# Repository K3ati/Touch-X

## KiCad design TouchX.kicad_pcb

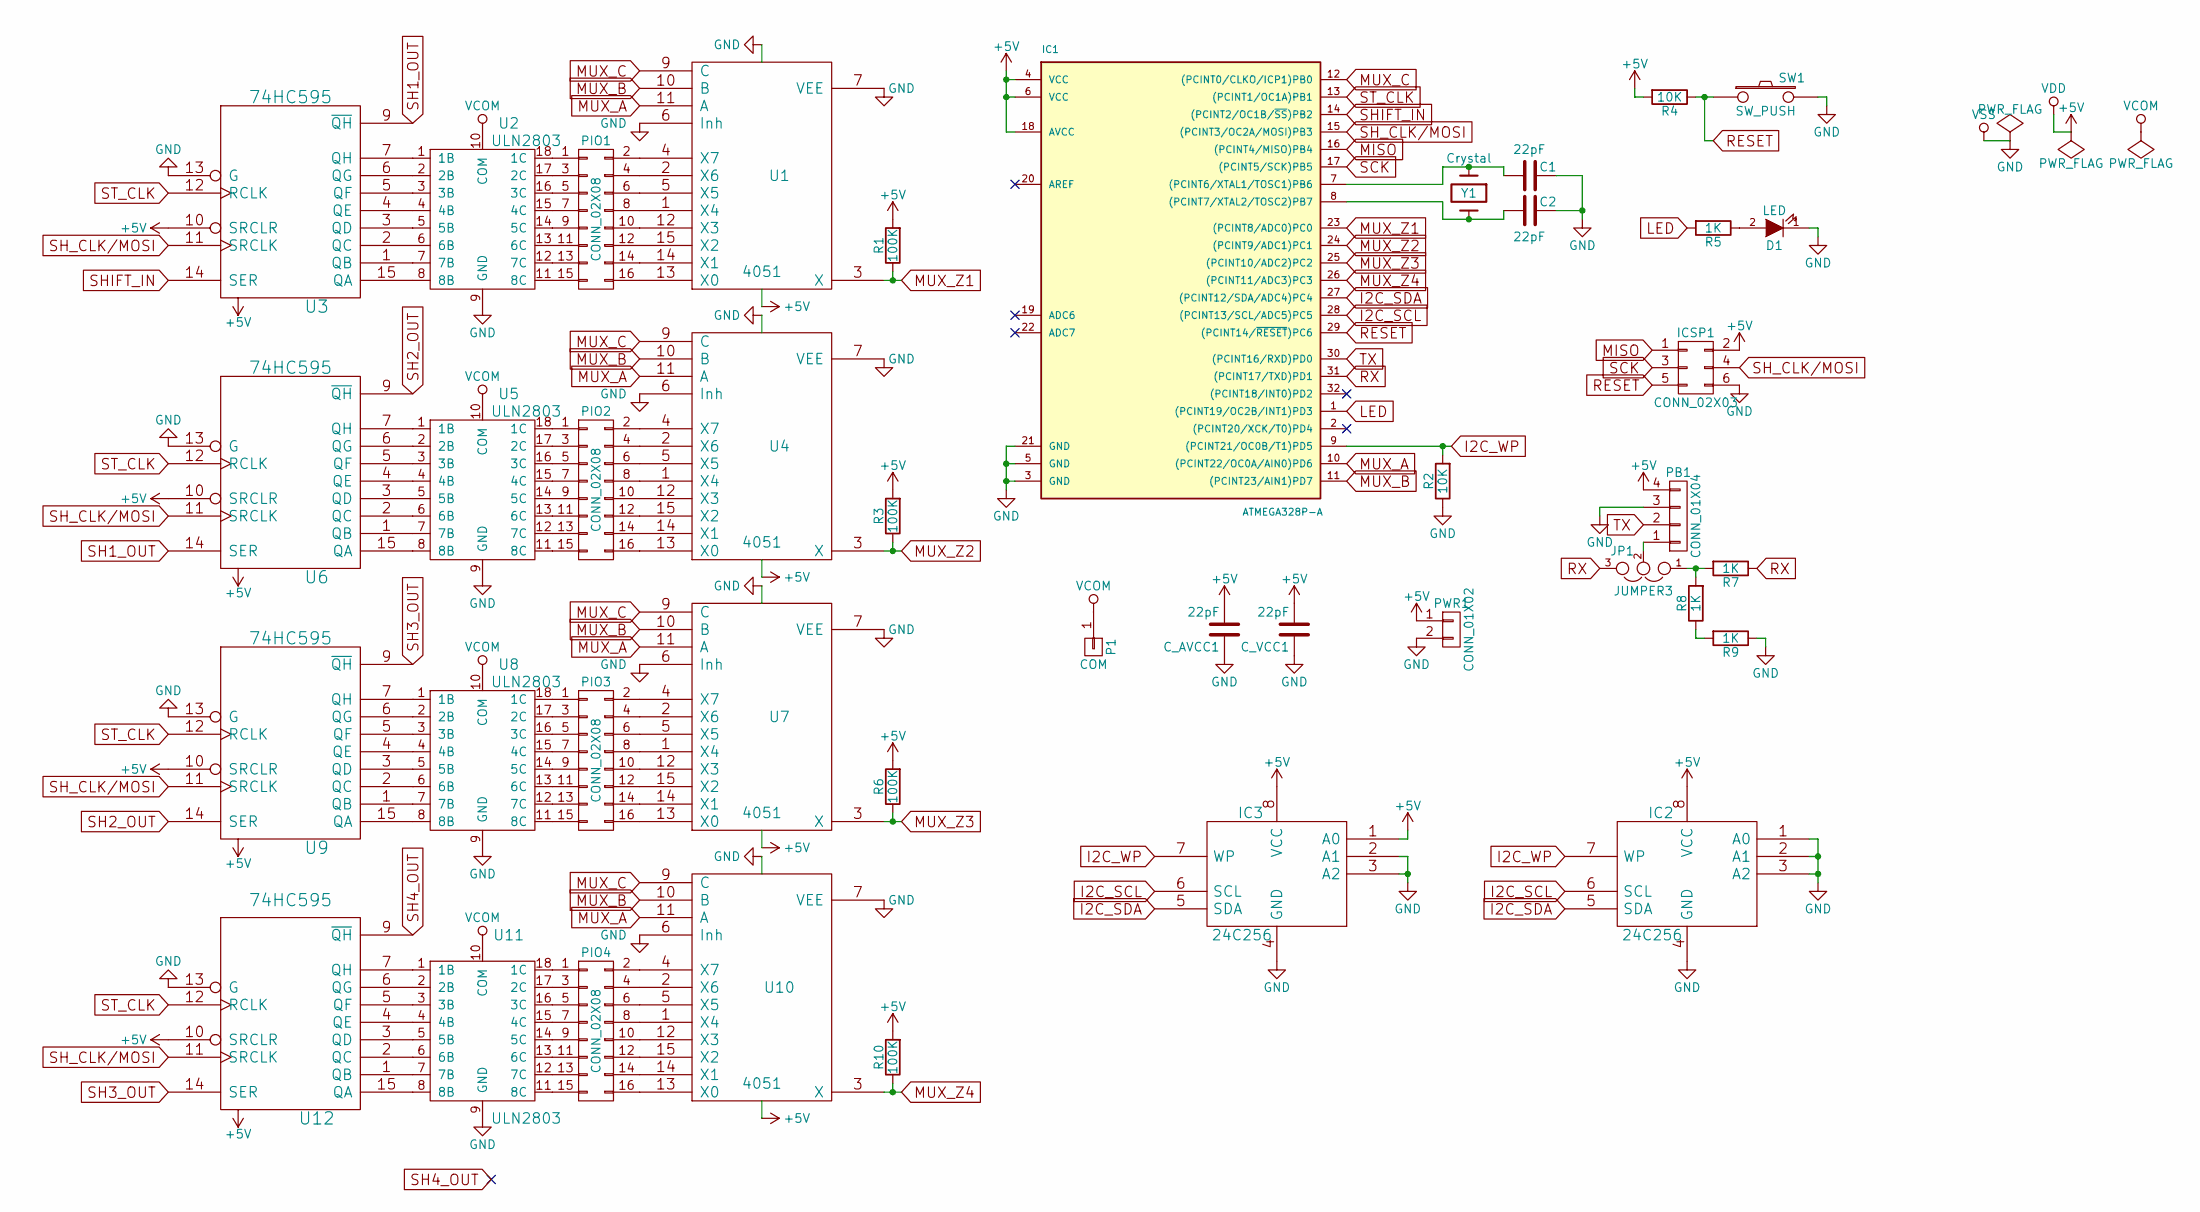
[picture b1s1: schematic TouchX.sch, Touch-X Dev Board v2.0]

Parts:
C1, C2: 22pF; c_1206
C_AVCC1: 22pF; c_1206
C_VCC1: 22pF; c_1206
D1: LED; Led_0805
IC1: ATMEGA328P-A; lqfp32
IC2, IC3: 24C256; so-8
ICSP1: CONN_02X03; pin_socket_3x2
JP1: JUMPER3; NetTie-II_SMD
P1: COM; Measurement_Point_Square-TH_Big
PB1: CONN_01X04; pin_socket_4
PIO1, PIO2, PIO3, PIO4: CONN_02X08; pin_socket_8x2
PWR1: CONN_01X02; pin_strip_2
R1, R3, R6, R10: 100K; r_1206
R2, R4: 10K; r_1206
R5, R7, R8, R9: 1K; r_1206
SW1: SW_PUSH; smd_push2
U1, U4, U7, U10: 4051; so-16
U2, U5, U8, U11: ULN2803; uln2803
U3, U6, U9, U12: 74HC595; so-16
Y1: Crystal; crystal_hc-49s

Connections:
+5V: C_AVCC1.2, C_VCC1.2, IC1.4 (VCC), IC1.6 (VCC), IC1.18 (AVCC), IC2.8 (VCC), IC3.1 (A0), IC3.8 (VCC), ICSP1.2, PB1.4, PWR1.1, R1.2, R3.2, R4.2, R6.2, R10.2, U1.16 (VDD), U3.10 (SRCLR), U3.16 (VCC), U4.16 (VDD), U6.10 (SRCLR), U6.16 (VCC), U7.16 (VDD), U9.10 (SRCLR), U9.16 (VCC), U10.16 (VDD), U12.10 (SRCLR), U12.16 (VCC)
GND: C1.1, C2.1, C_AVCC1.1, C_VCC1.1, D1.1 (K), IC1.3 (GND), IC1.5 (GND), IC1.21 (GND), IC2.1 (A0), IC2.2 (A1), IC2.3 (A2), IC2.4 (GND), IC3.2 (A1), IC3.3 (A2), IC3.4 (GND), ICSP1.6, PB1.3, PWR1.2, R2.1, R9.1, SW1.2, U1.6 (Inh), U1.7 (VEE), U1.8 (VSS), U2.9 (GND), U3.8 (GND), U3.13 (G), U4.6 (Inh), U4.7 (VEE), U4.8 (VSS), U5.9 (GND), U6.8 (GND), U6.13 (G), U7.6 (Inh), U7.7 (VEE), U7.8 (VSS), U8.9 (GND), U9.8 (GND), U9.13 (G), U10.6 (Inh), U10.7 (VEE), U10.8 (VSS), U11.9 (GND), U12.8 (GND), U12.13 (G)
I2C_SCL: IC1.28 ((PCINT13/SCL/ADC5)PC5), IC2.6 (SCL), IC3.6 (SCL)
I2C_SDA: IC1.27 ((PCINT12/SDA/ADC4)PC4), IC2.5 (SDA), IC3.5 (SDA)
I2C_WP: IC1.9 ((PCINT21/OC0B/T1)PD5), IC2.7 (WP), IC3.7 (WP), R2.2
LED: IC1.1 ((PCINT19/OC2B/INT1)PD3), R5.2
MISO: IC1.16 ((PCINT4/MISO)PB4), ICSP1.1
MUX_A: IC1.10 ((PCINT22/OC0A/AIN0)PD6), U1.11 (A), U4.11 (A), U7.11 (A), U10.11 (A)
MUX_B: IC1.11 ((PCINT23/AIN1)PD7), U1.10 (B), U4.10 (B), U7.10 (B), U10.10 (B)
MUX_C: IC1.12 ((PCINT0/CLKO/ICP1)PB0), U1.9 (C), U4.9 (C), U7.9 (C), U10.9 (C)
MUX_Z1: IC1.23 ((PCINT8/ADC0)PC0), R1.1, U1.3 (X)
MUX_Z2: IC1.24 ((PCINT9/ADC1)PC1), R3.1, U4.3 (X)
MUX_Z3: IC1.25 ((PCINT10/ADC2)PC2), R6.1, U7.3 (X)
MUX_Z4: IC1.26 ((PCINT11/ADC3)PC3), R10.1, U10.3 (X)
unnamed: C1.2, IC1.7 ((PCINT6/XTAL1/TOSC1)PB6), Y1.1
unnamed: C2.2, IC1.8 ((PCINT7/XTAL2/TOSC2)PB7), Y1.2
unnamed: D1.2 (A), R5.1
unnamed: JP1.1, R7.2, R8.2
unnamed: JP1.2, PB1.1
unnamed: PIO1.1, U2.18 (1C)
unnamed: PIO1.2, U1.4 (X7)
unnamed: PIO1.3, U2.17 (2C)
unnamed: PIO1.4, U1.2 (X6)
unnamed: PIO1.5, U2.16 (3C)
unnamed: PIO1.6, U1.5 (X5)
unnamed: PIO1.7, U2.15 (4C)
unnamed: PIO1.8, U1.1 (X4)
unnamed: PIO1.9, U2.14 (5C)
unnamed: PIO1.10, U1.12 (X3)
unnamed: PIO1.11, U2.13 (6C)
unnamed: PIO1.12, U1.15 (X2)
unnamed: PIO1.13, U2.12 (7C)
unnamed: PIO1.14, U1.14 (X1)
unnamed: PIO1.15, U2.11 (8C)
unnamed: PIO1.16, U1.13 (X0)
unnamed: PIO2.1, U5.18 (1C)
unnamed: PIO2.2, U4.4 (X7)
unnamed: PIO2.3, U5.17 (2C)
unnamed: PIO2.4, U4.2 (X6)
unnamed: PIO2.5, U5.16 (3C)
unnamed: PIO2.6, U4.5 (X5)
unnamed: PIO2.7, U5.15 (4C)
unnamed: PIO2.8, U4.1 (X4)
unnamed: PIO2.9, U5.14 (5C)
unnamed: PIO2.10, U4.12 (X3)
unnamed: PIO2.11, U5.13 (6C)
unnamed: PIO2.12, U4.15 (X2)
unnamed: PIO2.13, U5.12 (7C)
unnamed: PIO2.14, U4.14 (X1)
unnamed: PIO2.15, U5.11 (8C)
unnamed: PIO2.16, U4.13 (X0)
unnamed: PIO3.1, U8.18 (1C)
unnamed: PIO3.2, U7.4 (X7)
unnamed: PIO3.3, U8.17 (2C)
unnamed: PIO3.4, U7.2 (X6)
unnamed: PIO3.5, U8.16 (3C)
unnamed: PIO3.6, U7.5 (X5)
unnamed: PIO3.7, U8.15 (4C)
unnamed: PIO3.8, U7.1 (X4)
unnamed: PIO3.9, U8.14 (5C)
unnamed: PIO3.10, U7.12 (X3)
unnamed: PIO3.11, U8.13 (6C)
unnamed: PIO3.12, U7.15 (X2)
unnamed: PIO3.13, U8.12 (7C)
unnamed: PIO3.14, U7.14 (X1)
unnamed: PIO3.15, U8.11 (8C)
unnamed: PIO3.16, U7.13 (X0)
unnamed: PIO4.1, U11.18 (1C)
unnamed: PIO4.2, U10.4 (X7)
unnamed: PIO4.3, U11.17 (2C)
unnamed: PIO4.4, U10.2 (X6)
unnamed: PIO4.5, U11.16 (3C)
unnamed: PIO4.6, U10.5 (X5)
unnamed: PIO4.7, U11.15 (4C)
unnamed: PIO4.8, U10.1 (X4)
unnamed: PIO4.9, U11.14 (5C)
unnamed: PIO4.10, U10.12 (X3)
unnamed: PIO4.11, U11.13 (6C)
unnamed: PIO4.12, U10.15 (X2)
unnamed: PIO4.13, U11.12 (7C)
unnamed: PIO4.14, U10.14 (X1)
unnamed: PIO4.15, U11.11 (8C)
unnamed: PIO4.16, U10.13 (X0)
unnamed: R8.1, R9.2
unnamed: U2.1 (1B), U3.7 (QH)
unnamed: U2.2 (2B), U3.6 (QG)
unnamed: U2.3 (3B), U3.5 (QF)
unnamed: U2.4 (4B), U3.4 (QE)
unnamed: U2.5 (5B), U3.3 (QD)
unnamed: U2.6 (6B), U3.2 (QC)
unnamed: U2.7 (7B), U3.1 (QB)
unnamed: U2.8 (8B), U3.15 (QA)
unnamed: U5.1 (1B), U6.7 (QH)
unnamed: U5.2 (2B), U6.6 (QG)
unnamed: U5.3 (3B), U6.5 (QF)
unnamed: U5.4 (4B), U6.4 (QE)
unnamed: U5.5 (5B), U6.3 (QD)
unnamed: U5.6 (6B), U6.2 (QC)
unnamed: U5.7 (7B), U6.1 (QB)
unnamed: U5.8 (8B), U6.15 (QA)
unnamed: U8.1 (1B), U9.7 (QH)
unnamed: U8.2 (2B), U9.6 (QG)
unnamed: U8.3 (3B), U9.5 (QF)
unnamed: U8.4 (4B), U9.4 (QE)
unnamed: U8.5 (5B), U9.3 (QD)
unnamed: U8.6 (6B), U9.2 (QC)
unnamed: U8.7 (7B), U9.1 (QB)
unnamed: U8.8 (8B), U9.15 (QA)
unnamed: U11.1 (1B), U12.7 (QH)
unnamed: U11.2 (2B), U12.6 (QG)
unnamed: U11.3 (3B), U12.5 (QF)
unnamed: U11.4 (4B), U12.4 (QE)
unnamed: U11.5 (5B), U12.3 (QD)
unnamed: U11.6 (6B), U12.2 (QC)
unnamed: U11.7 (7B), U12.1 (QB)
unnamed: U11.8 (8B), U12.15 (QA)
RESET: IC1.29 ((PCINT14/~RESET~)PC6), ICSP1.5, R4.1, SW1.1
RX: IC1.31 ((PCINT17/TXD)PD1), JP1.3, R7.1
SCK: IC1.17 ((PCINT5/SCK)PB5), ICSP1.3
SH1_OUT: U3.9 (~QH), U6.14 (SER)
SH2_OUT: U6.9 (~QH), U9.14 (SER)
SH3_OUT: U9.9 (~QH), U12.14 (SER)
SHIFT_IN: IC1.14 ((PCINT2/OC1B/~SS~)PB2), U3.14 (SER)
SH_CLK/MOSI: IC1.15 ((PCINT3/OC2A/MOSI)PB3), ICSP1.4, U3.11 (SRCLK), U6.11 (SRCLK), U9.11 (SRCLK), U12.11 (SRCLK)
ST_CLK: IC1.13 ((PCINT1/OC1A)PB1), U3.12 (RCLK), U6.12 (RCLK), U9.12 (RCLK), U12.12 (RCLK)
TX: IC1.30 ((PCINT16/RXD)PD0), PB1.2
VCOM: P1.1, U2.10 (COM), U5.10 (COM), U8.10 (COM), U11.10 (COM)

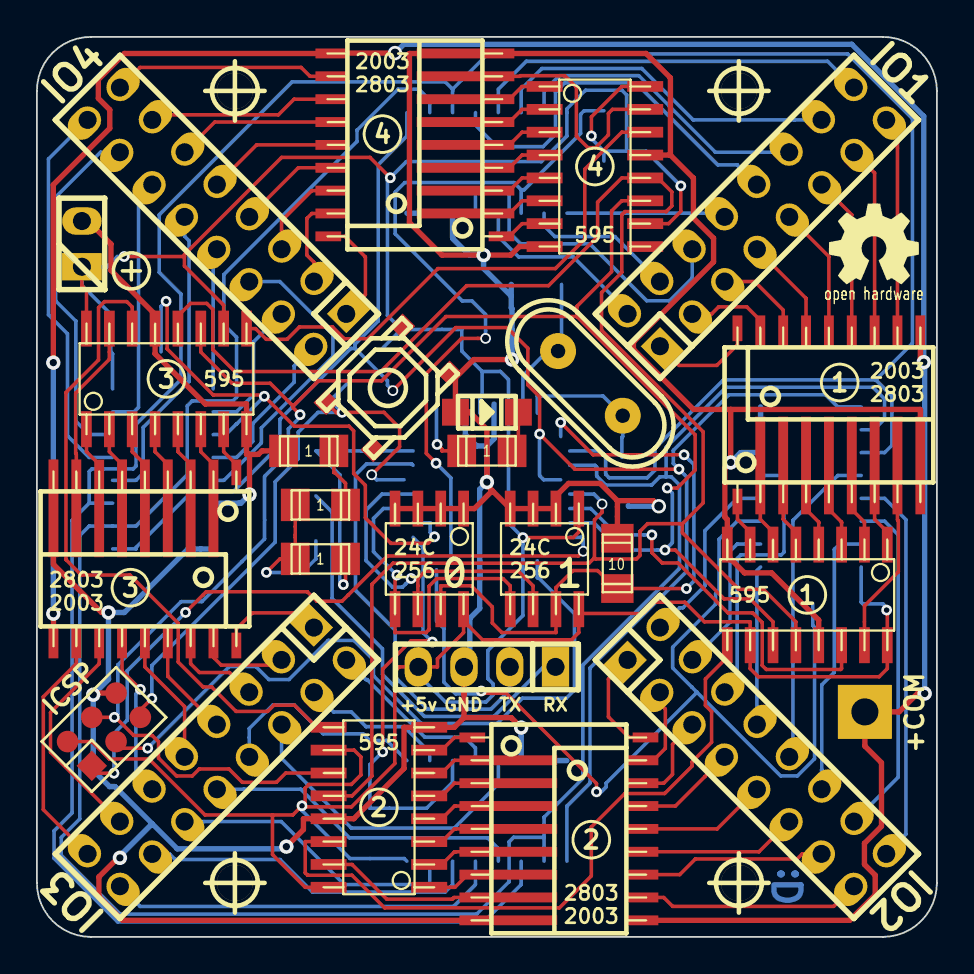
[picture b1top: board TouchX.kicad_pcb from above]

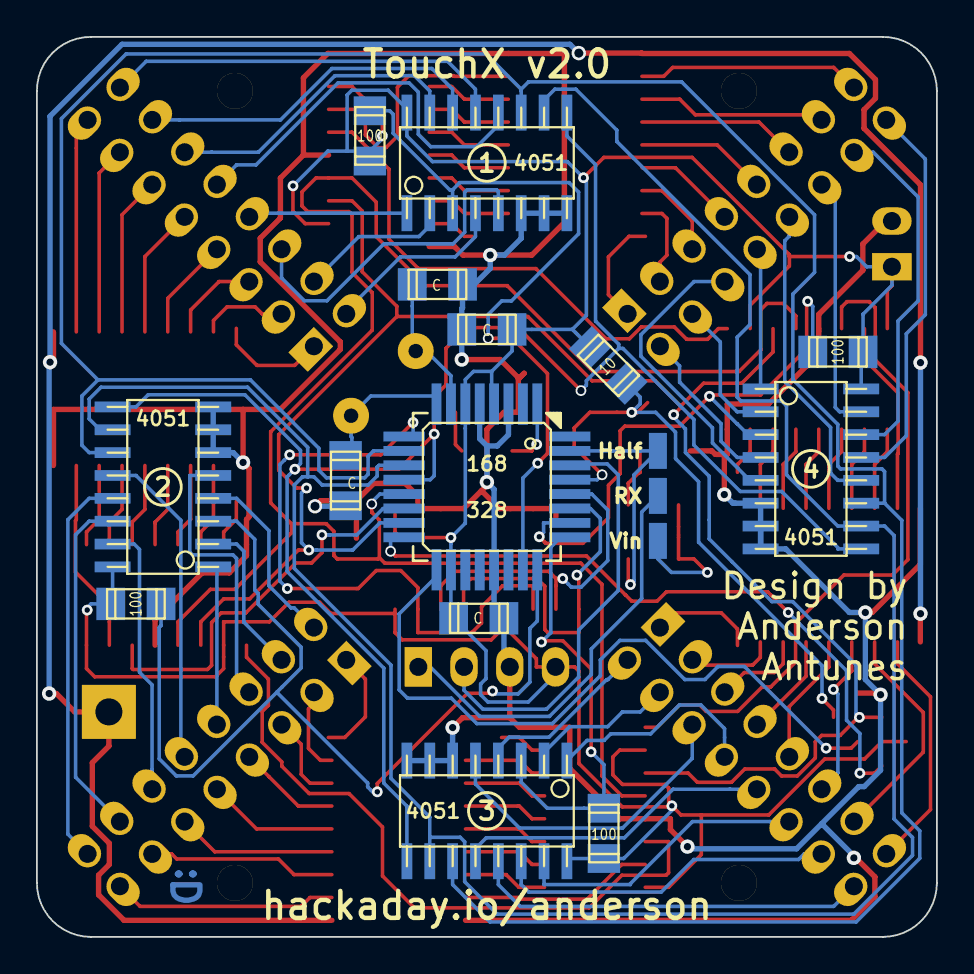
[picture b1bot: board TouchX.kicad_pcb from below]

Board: 2 copper layers, 50.0 x 50.0 mm, 46 parts (15 on the bottom side), 127 nets.

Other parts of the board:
G1: LOGO; Logo_silk_OSHW_6x6mm
hole_2mm1: h1; hole_2mm
hole_2mm2: h2; hole_2mm
hole_2mm3: h3; hole_2mm
hole_2mm4: h4; hole_2mm

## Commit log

2015-05-30 First commit, added license file and touch-x board kicad project rev2

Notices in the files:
TouchX.kicad_pcb:
Copyright 2015 Anderson de Oliveira Antunes
Copyrights: CC-BY-SA 4.0 Patents: Apache 2.0
